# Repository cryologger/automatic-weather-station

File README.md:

# Cryologger - Automatic Weather Station (AWS)

### Note: This project is under active development.

## 1.0 Introduction
Polar environments are undergoing rapid environmental change, yet there is a lack of high spatial and temporal monitoring data available in these remote regions. Reliance on expensive and proprietary commercial data acquisition and telemetry systems can inhibit both researchers and citizen scientists and present a significant barrier to the establishment of widespread monitoring networks. The development of low-cost, open-source instrumentation can greatly reduce the cost of cryospheric research, improve the spatial density and coverage of collected data, and produce new ways to observe and monitor the cryosphere.

The Cryologger Automatic Weather Station (AWS), is an open-source datalogger and telemeter comprised of low-cost, off the shelf components that is capable of supporting the physical measurement needs of a variety of cryospheric scientific applications when configured as an automatic weather station (AWS).

## 2.0 Methods

### 2.1 Design
The Cryologger AWS is based on the open-source Arduino platform (www.arduino.cc) and built using low-cost, do-it-yourself electronics that can be easily modified to meet the needs of the end-user. Code was written using the Arduino Integrated Development Environment (IDE) and benefits from the availability of community-generated libraries.

Planned for extended deployments in harsh Arctic conditions, the Cryologger AWS provides long-term measurements of weather variables such as temperature, humidity, wind speed, wind direction, solar irradiance and snow depth, as well as system diagnostic variables including pitch, roll, battery voltage. Data are transmitted over the Iridium satellite network at specified intervals and can be remotely updated based on the desired sampling frequency. Collected data are made available in near-real time at https://cryologger.org.

#### 2.1.1. Bill of Materials (BOM)

For a complete bill of materials, including requirements for power and mounting of a complete deployable system, please see ASSEMBLY.md.

**Table 1.** Bill of materials and associated costs for the main components used in the Cryologger AWS v1.0. Prices are listed in USD and are current as of December 2023. Taxes and shipping not included. <sup>1</sup>Denotes optional component.
| Component             | Product                                                                                                                      | Quantity | Cost (USD) |
|-----------------------|------------------------------------------------------------------------------------------------------------------------------|:--------:|:----------:|
| PCB                   | [Custom Cryologger Printed Circuit Board](https://jlcpcb.com)                                                                |     1    |    $5.00   |
| Satellite transceiver | [Rock7 RockBLOCK 9603](http://www.rock7mobile.com/products-rockblock-9603)                                                   |     1    |   $267.50  |
| Satellite antenna     | [Maxtena M1621HCT-P-SMA](https://maxtena.com/products/f-passive/m1621hct-p-sma-iridium-passive-antenna/)                     |     1    |   $54.00   |
| Processor             | [Adafruit Feather M0 Adalogger](https://www.adafruit.com/product/2796)                                                       |     1    |   $19.95   |
| GNSS                  | [Adafruit Ultimate GPS FeatherWing](https://www.adafruit.com/product/3133)                                                   |     1    |   $24.95   |
| IMU                   | [Adafruit LSM303AGR Accelerometer Magnetometer](https://www.adafruit.com/product/4413)                                       |     1    |   $12.50   |
| Sensor                | [Adafruit BME280 Temperature Humidity Pressure Sensor ](https://www.adafruit.com/product/2652)                               |     1    |   $14.95   |
| Voltage regulator     | [Pololu D36V6F3 3.3V 600mA Step-Down Voltage Regulator](https://www.pololu.com/product/3791)                                 |     1    |   $16.95   |
| Voltage regulator     | [Pololu D36V6F5 5V 600mA Step-Down Voltage Regulator](https://www.pololu.com/product/3792)                                   |     1    |   $16.95   |
| Voltage regulator     | [Pololu U3V40F12 12V Step-Up Voltage Regulator ](https://www.pololu.com/product/4016)                                        |     1    |    $9.95   |
| Resistor              | [10 M 1% 0.6 W resistor](https://www.mouser.ca/ProductDetail/594-MBB02070C1005FCT)                                           |     1    |    $0.44   |
| Resistor              | [1 M 1% 0.6 W resistor](https://www.mouser.ca/ProductDetail/594-B0207C1M000F5T)                                              |     1    |    $0.40   |
| Capacitor             | [0.1 uF Capacitor](https://www.mouser.ca/ProductDetail/Vishay-BC-Components/K104K15X7RF53L2?qs=mWFvmKOfYW8KbAXlf9eSQA%3D%3D) |     1    |    $0.29   |
| Power connector       |                                                                                                                              |     1    |            |
| Power connector       |                                                                                                                              |     1    |            |
| Connector             |                                                                                                                              |     1    |            |

**Table 2.** Environmental sensors used in Cryologger AWS v1.0. Prices are listed in USD and are current as of December 2023. Taxes and shipping not included.
| Environment Variable          | Sensor                                                                                                                       | Cost (USD) |
|-------------------------------|------------------------------------------------------------------------------------------------------------------------------|:----------:|
| Wind Speed & Direction        | [RM Young Wind Monitor 5103L Anemometer](https://www.youngusa.com/product/wind-monitor/)                                     | $1432      |
| Temperature/Relative Humidity | [Vaisala HMP60 Humidity and Temperature Probe](https://store.vaisala.com/en/products/HMP60)                                  | $330       |
| Solar Irradiance              | [SP-212-SS: Amplified 0-2.5 Volt Pyranometer](https://www.apogeeinstruments.com/sp-212-ss-amplified-0-2-5-volt-pyranometer/) | $325       |
| Snow Depth                    | [Maxboxtix MB7374 HRXL-MaxSonar-WRST7](https://maxbotix.com/products/mb7374)                                                 | $290       |

### 2.2 Operation
When initially powered on, the Cryologger AWS will attempt to establish a GNSS fix and sychronize the real-time clock (RTC) for up to 5 minutes. Once the RTC is synchronized, the system will set an alarm to wake at the user-specified time and then enter a low-power deep sleep. Nominally, the system will wake every 5 minutes, obtain measurements from all sensors, and log data to a microSD card. Measurements are averaged each hour and transmitted  

While the system is in deep sleep, a Watchdog Timer (WDT) will wake the system to check the program has not frozen every 8 seconds and perform a reset, if necessary. This helps to ensure the long-term reliability of the system.

#### 2.2.1 Measurements

**Table 2.** List of Cryologger AWS v1.0 data variables that can be transmitted and/or logged with variable sizes.

| Type     | Variable          | Description                        | Size (bytes) |
|----------|-------------------|------------------------------------|:------------:|
| uint32_t | unixtime          | UNIX Epoch time                    |       4      |
| int16_t  | temperatureInt    | Internal temperature (°C)          |       2      |
| uint16_t | humidityInt       | Internal humidity (%)              |       2      |
| uint16_t | pressureInt       | Internal pressure (hPa)            |       2      |
| int16_t  | temperatureExt    | External temperature (°C)          |       2      |
| uint16_t | humidityExt       | External humidity (%)              |       2      |
| int16_t  | pitch             | Pitch (°)                          |       2      |
| int16_t  | roll              | Roll (°)                           |       2      |
| uint16_t | solar             | Solar irradiance (W m-2)           |       2      |
| uint16_t | windSpeed         | Mean wind speed (m/s)              |       2      |
| uint16_t | windDirection     | Mean wind direction (°)            |       2      |
| uint16_t | windGustSpeed     | Wind gust speed (m/s)              |       2      |
| uint16_t | windGustDirection | Wind gust direction (°)            |       2      |
| int32_t  | latitude          | Latitude (DD)                      |       4      |
| int32_t  | longitude         | Longitude (DD)                     |       4      |
| uint8_t  | satellites        | Number of satellites               |       1      |
| uint16_t | hdop              | HDOP                               |       2      |
| uint16_t | voltage           | Battery voltage (V)                |       2      |
| uint16_t | transmitDuration  | Previous transmission duration (s) |       2      |
| uint8_t  | transmitStatus    | Iridium return code                |       1      |
| uint16_t | iterationCounter  | Message counter                    |       2      |

#### 2.2.2 Data Transmission and Processing

Sensor measurements and GNSS position are recorded hourly and stored in memory until the desired transmission interval is reached. Data are compressed into a binary message (340 bytes maximum) to minimize the cost and total number of transmissions required. Data are transmitted via the Iridium Short Burst Data (SBD) satellite network at user-specified intervals, which can be remotely updated based on the desired sampling frequency. SBD data messages are received by an Iridium ground station and sent to Ground Control's server. The data is then forwarded to an Amazon Web Services (AWS) SQS queue, decoded using an AWS Lambda Python function and stored in a database using the Amazon Relational Database Service (RDS). Data can be viewed in near-real time at https://cryologger.org.

## 3.0 Deployments

<p align="center"><b>Figure 3.</b> Map of Cryologger AWS deployments made between 2019 and 2023.</p>

## 4.0 Results

## 5.0 Conclusion

## Repository Contents

* **/Documentation** - Assembly, deployment and troubleshoting guides, as well as information of components used and associated costs.

* **/Hardware** - KiCad PCB schematic and design files.

* **/Software** - Arduino code and Python data analysis scripts.

## License Information
Cryologger code, firmware, and software is licensed under the GNU General Public License v3.0 (https://www.gnu.org/licenses/gpl-3.0.en.html). 

<p xmlns:cc="http://creativecommons.org/ns#" >Cryologger hardware is licensed under <a href="https://creativecommons.org/licenses/by-nc-sa/4.0/?ref=chooser-v1" target="_blank" rel="license noopener noreferrer" style="display:inline-block;">CC BY-NC-SA 4.0 </a></p>

Cheers,

**Adam**

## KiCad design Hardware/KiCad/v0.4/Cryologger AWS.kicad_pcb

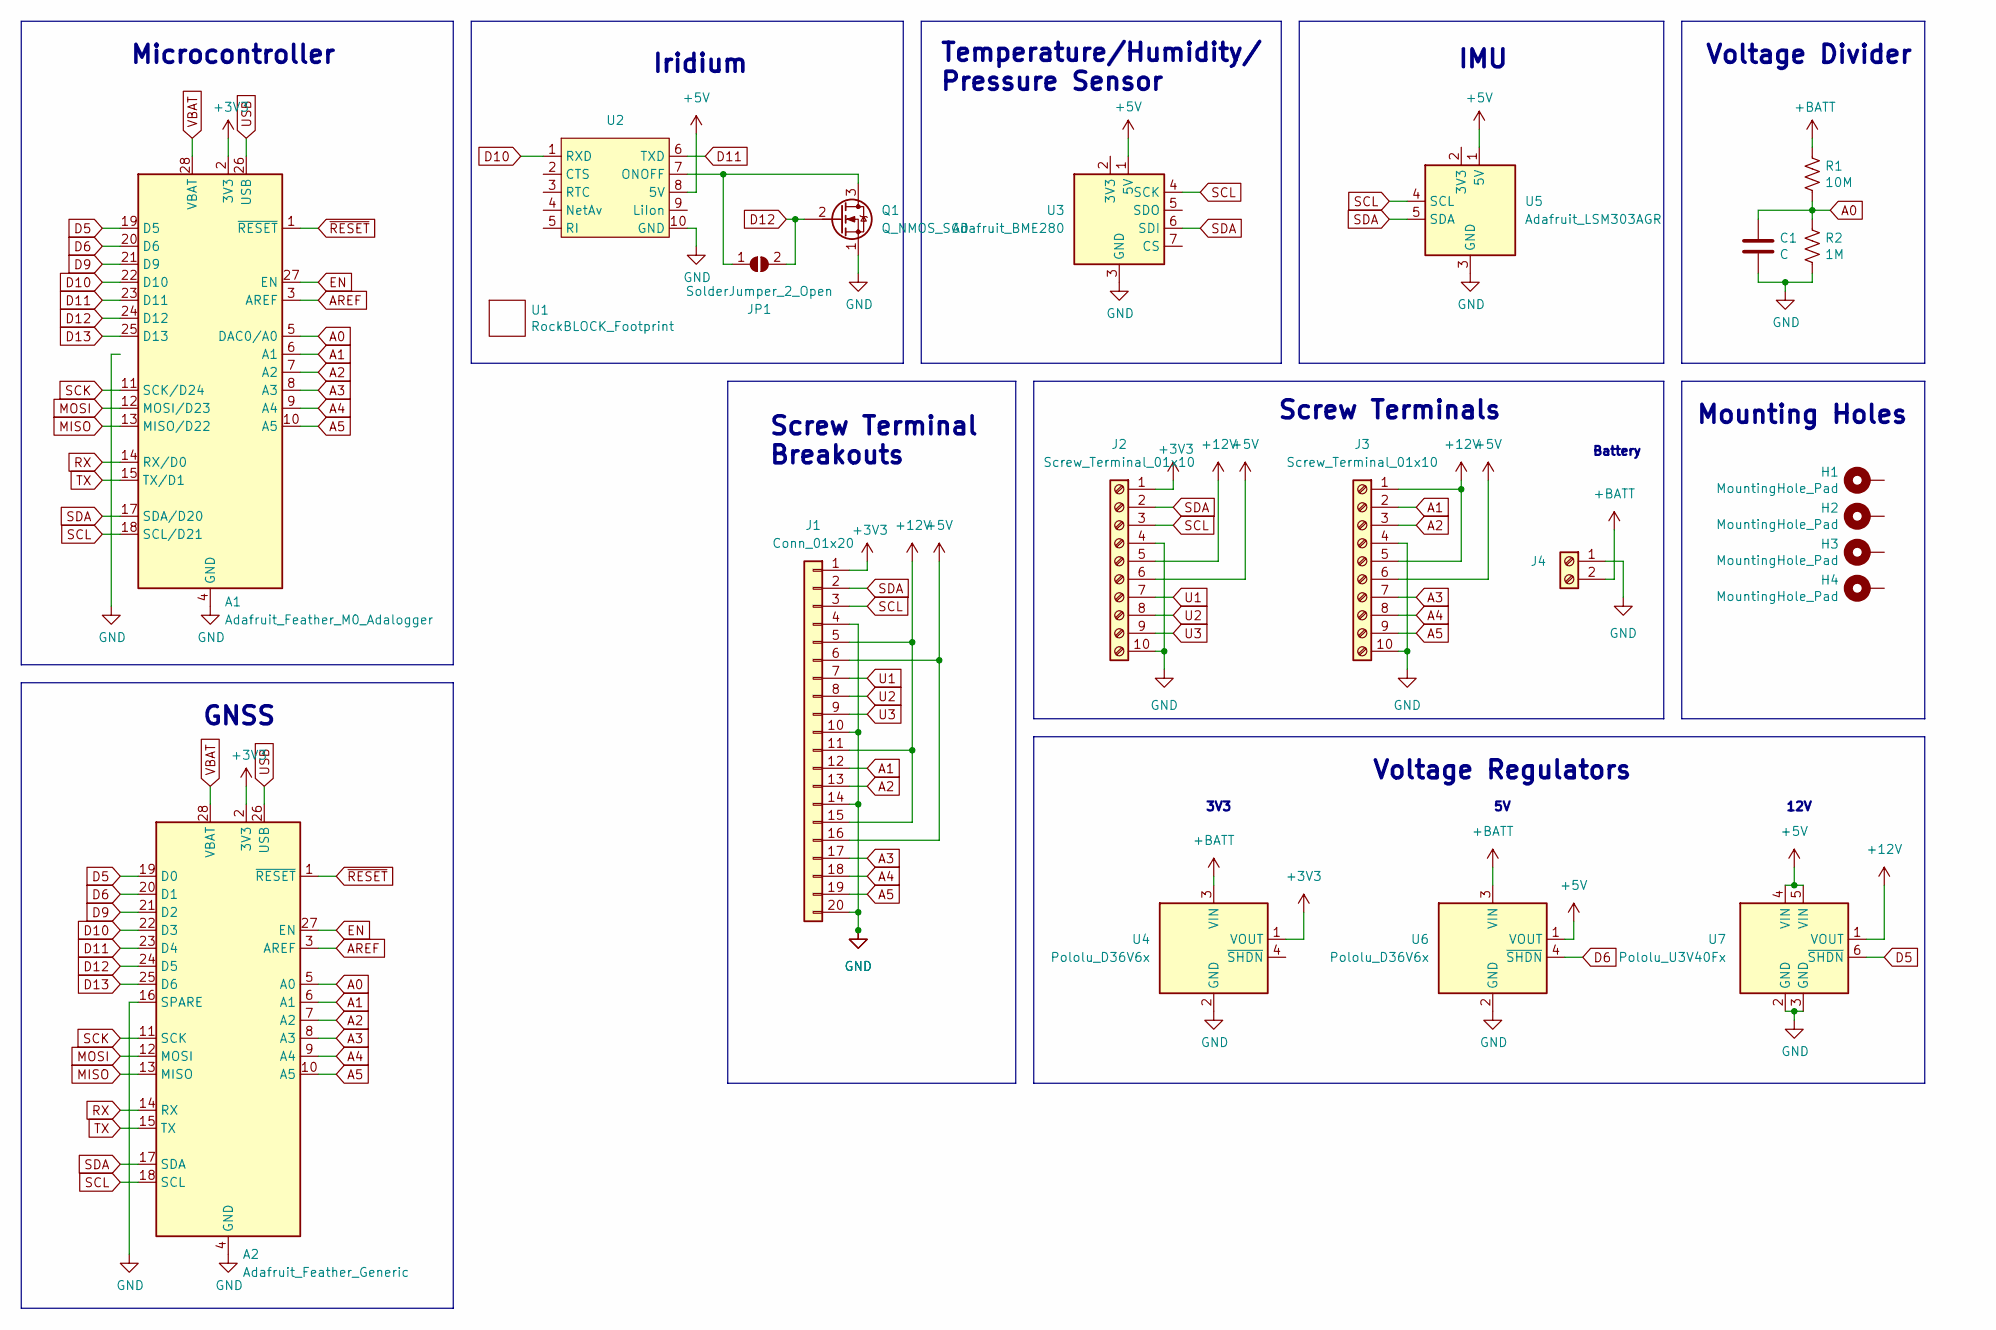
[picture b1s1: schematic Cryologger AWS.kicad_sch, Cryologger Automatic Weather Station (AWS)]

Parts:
A1: Adafruit_Feather_M0_Adalogger; Adafruit_Feather_Header_Double
A2: Adafruit_Feather_Generic; Adafruit_Feather_Header_Double
C1: C; C_Disc_D3.8mm_W2.6mm_P2.50mm
H1, H2, H3, H4: MountingHole_Pad; MountingHole_3mm_Pad
J1: Conn_01x20; Pin_1.0mm_10.0mm_1x20
J2, J3: Screw_Terminal_01x10; TerminalBlock_Phoenix_MKDS-1,5-10-5.08_1x10_P5.08mm_Horizon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
J4: Screw_Terminal_01x02; PhoenixContact_MSTBA_2,5_2-G-5,08_1x02_P5.08mm_Horizontal
JP1: SolderJumper_2_Open; SolderJumper-2_P1.3mm_Open_RoundedPad1.0x1.5mm
Q1: Q_NMOS_SGD; TO-92
R1: 10M; R_Axial_DIN0207_L6.3mm_D2.5mm_P10.16mm_Horizontal
R2: 1M; R_Axial_DIN0207_L6.3mm_D2.5mm_P10.16mm_Horizontal
U1: RockBLOCK_Footprint; RockBLOCK_9603
U2: Molex_PicoBlade_53047-1010_1x10_P1.25mm_Vertical
U3: Adafruit_BME280
U4, U6: Pololu_D36V6x
U5: Adafruit_LSM303AGR
U7: Pololu_U3V40Fx

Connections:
+3V3: A1.2 (3V3), A2.2 (3V3), J1.1, J2.1, U4.1 (VOUT)
+5V: J1.6, J1.16, J2.6, J3.6, U2.8 (5V), U3.1 (5V), U5.1 (5V), U6.1 (VOUT), U7.4 (VIN), U7.5 (VIN)
+12V: J1.5, J1.11, J1.15, J2.5, J3.1, J3.5, U7.1 (VOUT)
+BATT: J4.2, R1.1, U4.3 (VIN), U6.3 (VIN)
A0: A1.5 (DAC0/A0), A2.5 (A0), C1.1, R1.2, R2.1
A1: A1.6 (A1), A2.6 (A1), J1.12, J3.2
A2: A1.7 (A2), A2.7 (A2), J1.13, J3.3
A3: A1.8 (A3), A2.8 (A3), J1.17, J3.7
A4: A1.9 (A4), A2.9 (A4), J1.18, J3.8
A5: A1.10 (A5), A2.10 (A5), J1.19, J3.9
AREF: A1.3 (AREF), A2.3 (AREF)
D5: A1.19 (D5), A2.19 (D0), U7.6 (~SHDN)
D6: A1.20 (D6), A2.20 (D1), U6.4 (~SHDN)
D9: A1.21 (D9), A2.21 (D2)
D10: A1.22 (D10), A2.22 (D3), U2.1 (RXD)
D11: A1.23 (D11), A2.23 (D4), U2.6 (TXD)
D12: A1.24 (D12), A2.24 (D5), JP1.2 (B), Q1.2 (G)
D13: A1.25 (D13), A2.25 (D6)
EN: A1.27 (EN), A2.27 (EN)
GND: A1.4 (GND), A1.16 (GND), A2.4 (GND), A2.16 (SPARE), C1.2, J1.4, J1.10, J1.14, J1.20, J2.4, J2.10, J3.4, J3.10, J4.1, Q1.1 (S), R2.2, U2.10 (GND), U3.3 (GND), U4.2 (GND), U5.3 (GND), U6.2 (GND), U7.2 (GND), U7.3 (GND)
MISO: A1.13 (MISO/D22), A2.13 (MISO)
MOSI: A1.12 (MOSI/D23), A2.12 (MOSI)
unnamed: JP1.1 (A), Q1.3 (D), U2.7 (ONOFF)
RX: A1.14 (RX/D0), A2.14 (RX)
SCK: A1.11 (SCK/D24), A2.11 (SCK)
SCL: A1.18 (SCL/D21), A2.18 (SCL), J1.3, J2.3, U3.4 (SCK), U5.4 (SCL)
SDA: A1.17 (SDA/D20), A2.17 (SDA), J1.2, J2.2, U3.6 (SDI), U5.5 (SDA)
TX: A1.15 (TX/D1), A2.15 (TX)
U1: J1.7, J2.7
U2: J1.8, J2.8
U3: J1.9, J2.9
USB: A1.26 (USB), A2.26 (USB)
VBAT: A1.28 (VBAT), A2.28 (VBAT)
~RESET: A1.1 (~RESET), A2.1 (~RESET)

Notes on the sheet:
Screw Terminals
Iridium
Voltage Regulators
Voltage Divider
GNSS
IMU
Microcontroller
Screw Terminal Breakouts
3V3
Battery
Temperature/Humidity/ Pressure Sensor
12V
Mounting Holes

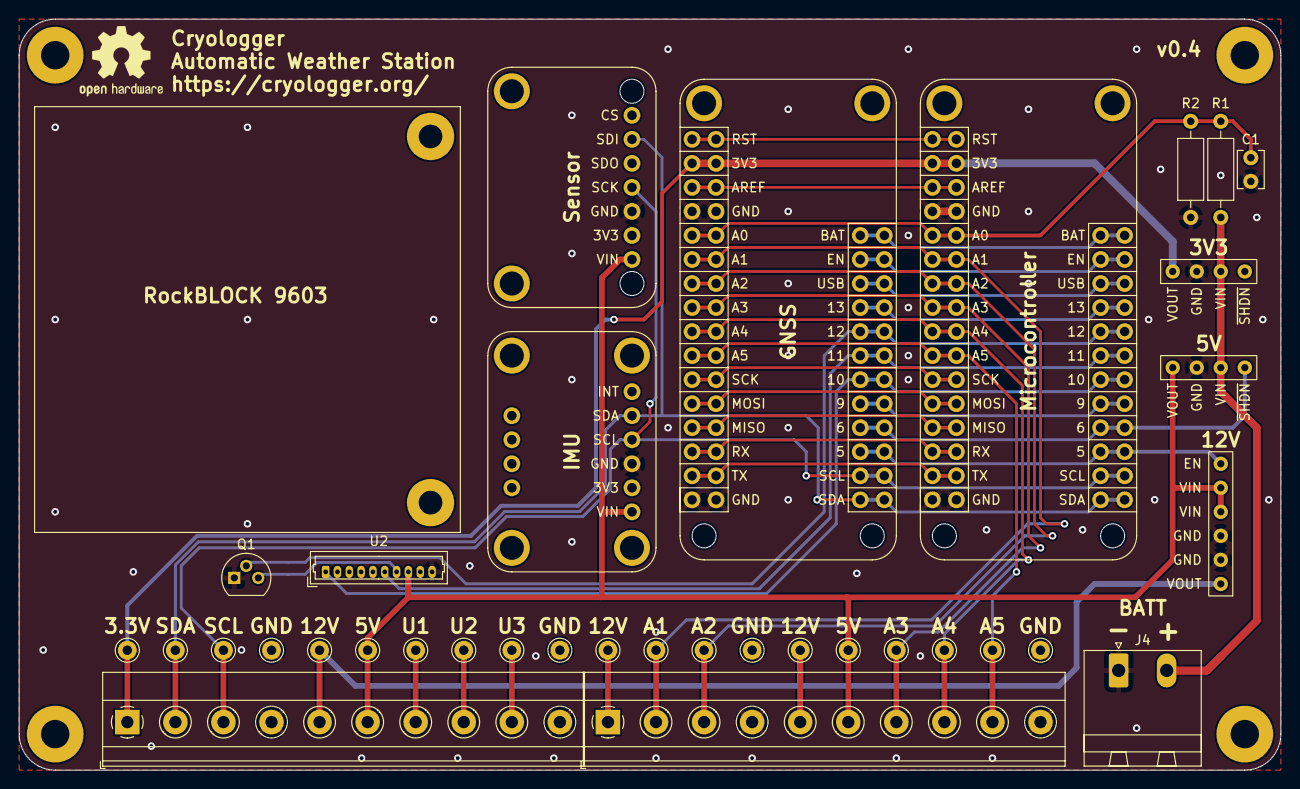
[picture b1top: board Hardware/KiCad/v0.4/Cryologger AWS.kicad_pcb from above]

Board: 2 copper layers, 133.3 x 79.4 mm, 22 parts (1 on the bottom side), 34 nets.

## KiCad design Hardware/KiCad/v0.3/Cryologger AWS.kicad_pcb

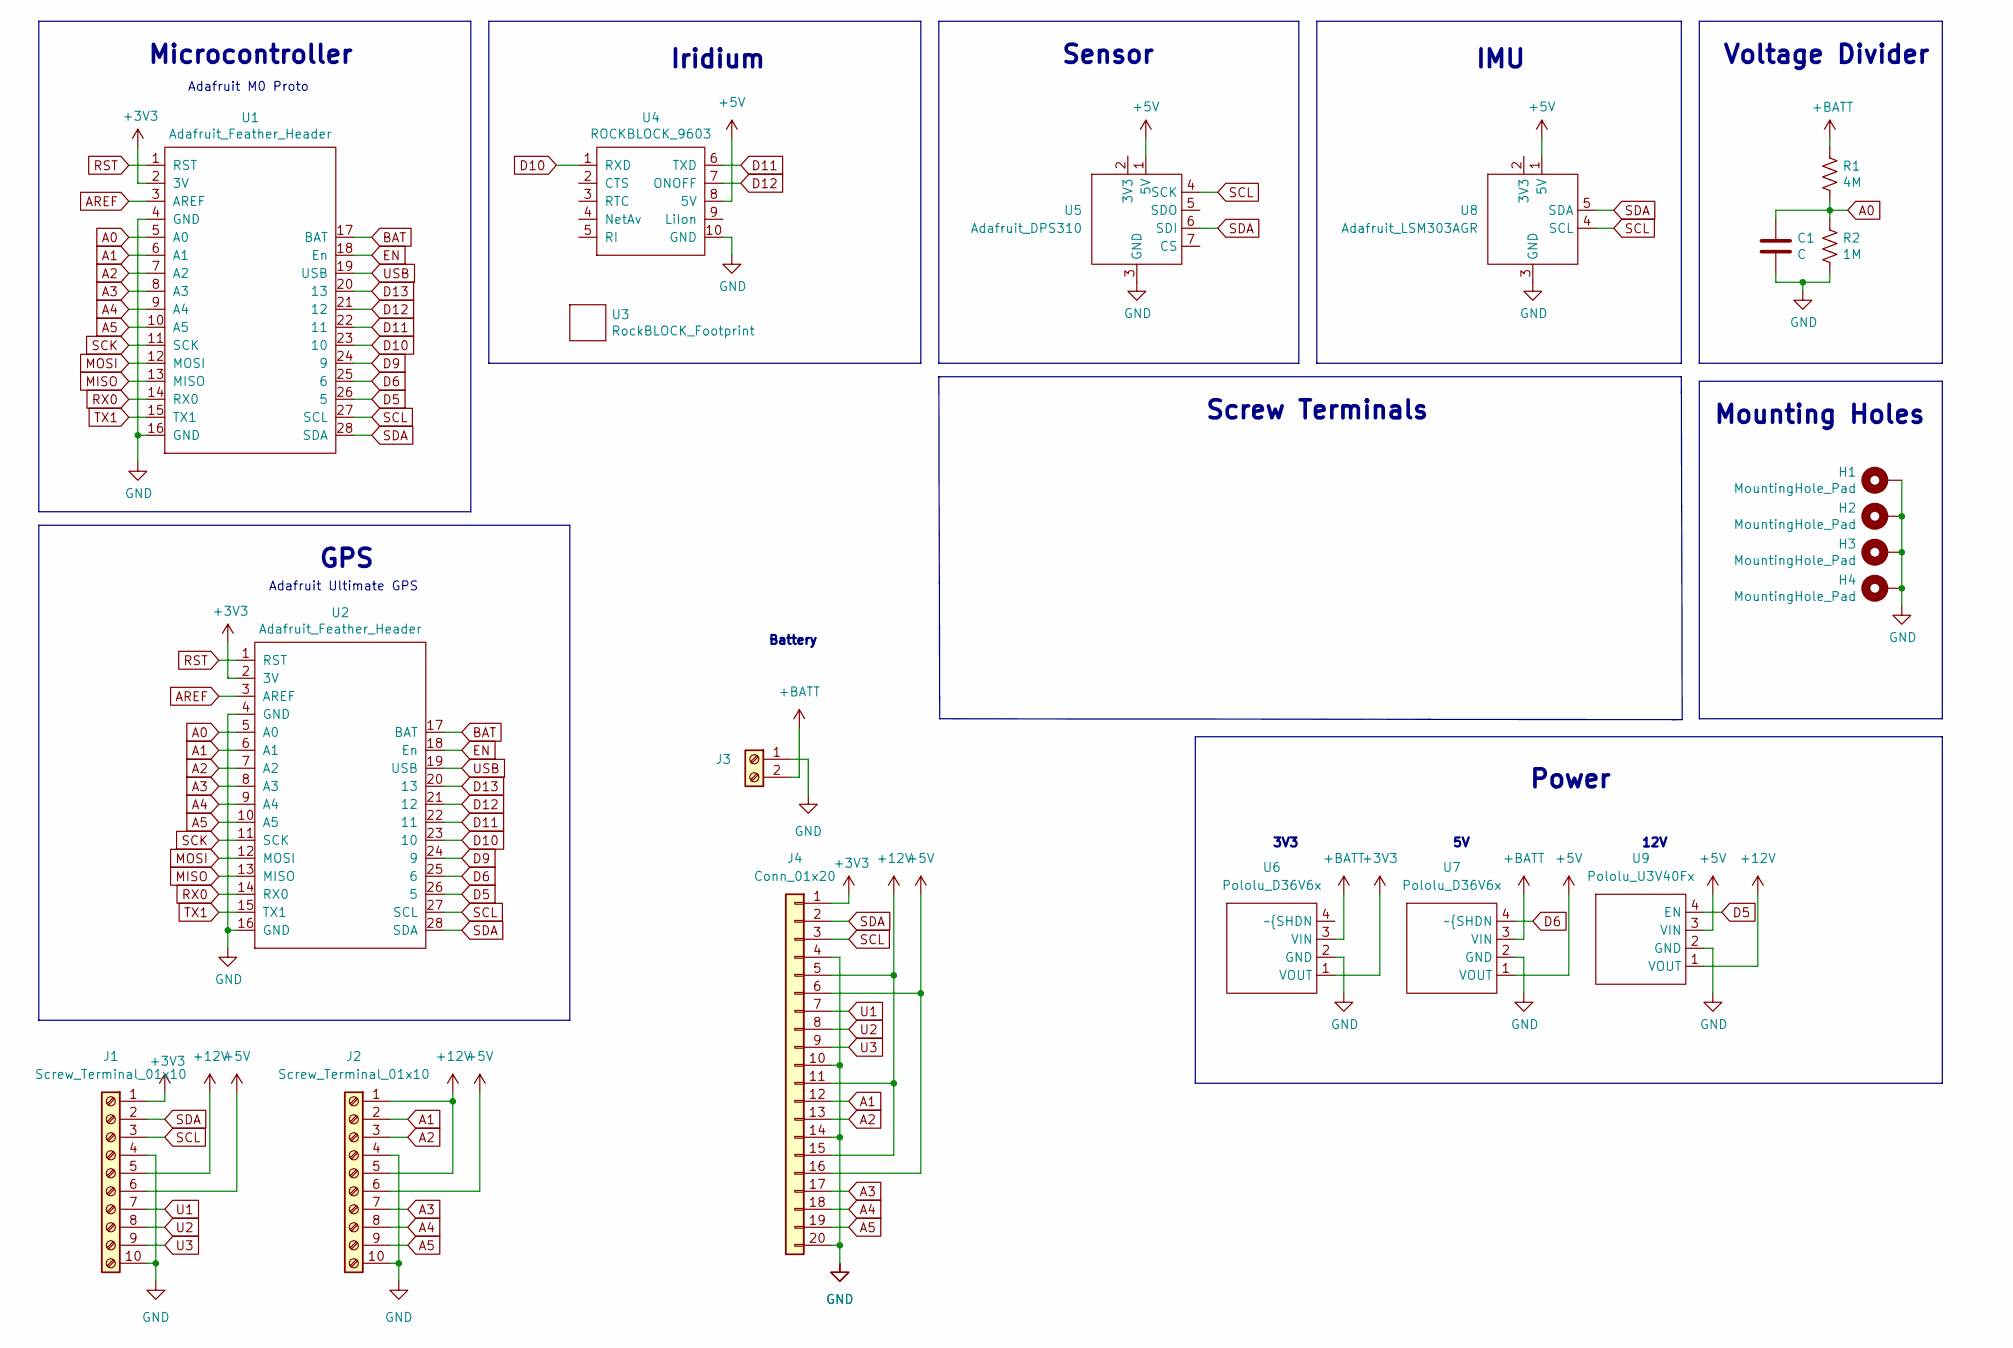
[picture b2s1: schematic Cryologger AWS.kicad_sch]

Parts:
C1: C; C_Disc_D3.8mm_W2.6mm_P2.50mm
H1, H2, H3, H4: MountingHole_Pad; MountingHole_3mm_Pad
J1, J2: Screw_Terminal_01x10; TerminalBlock_Phoenix_MKDS-1,5-10-5.08_1x10_P5.08mm_Horizon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
J3: Screw_Terminal_01x02; PhoenixContact_MSTBA_2,5_2-G-5,08_1x02_P5.08mm_Horizontal
J4: Conn_01x20; Pin_1.0mm_10.0mm_1x20
R1: 4M; R_Axial_DIN0207_L6.3mm_D2.5mm_P10.16mm_Horizontal
R2: 1M; R_Axial_DIN0207_L6.3mm_D2.5mm_P10.16mm_Horizontal
U1, U2: Adafruit_Feather_Header; Adafruit_Feather_Header_Double
U3: RockBLOCK_Footprint; RockBLOCK_9603
U4: ROCKBLOCK_9603; Molex_PicoBlade_53047-1010_1x10_P1.25mm_Vertical
U5: Adafruit_DPS310
U6, U7: Pololu_D36V6x
U8: Adafruit_LSM303AGR
U9: Pololu_U3V40Fx

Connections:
+3V3: J1.1, J4.1, U1.2 (3V), U2.2 (3V), U6.1 (VOUT)
+5V: J1.6, J2.6, J4.6, J4.16, U4.8 (5V), U5.1 (5V), U7.1 (VOUT), U8.1 (5V), U9.3 (VIN)
+12V: J1.5, J2.1, J2.5, J4.5, J4.11, J4.15, U9.1 (VOUT)
+BATT: J3.2, R1.1, U6.3 (VIN), U7.3 (VIN)
A0: C1.1, R1.2, R2.1, U1.5 (A0), U2.5 (A0)
A1: J2.2, J4.12, U1.6 (A1), U2.6 (A1)
A2: J2.3, J4.13, U1.7 (A2), U2.7 (A2)
A3: J2.7, J4.17, U1.8 (A3), U2.8 (A3)
A4: J2.8, J4.18, U1.9 (A4), U2.9 (A4)
A5: J2.9, J4.19, U1.10 (A5), U2.10 (A5)
AREF: U1.3 (AREF), U2.3 (AREF)
BAT: U1.17 (BAT), U2.17 (BAT)
D5: U1.26 (5), U2.26 (5), U9.4 (EN)
D6: U1.25 (6), U2.25 (6), U7.4 (~{SHDN)
D9: U1.24 (9), U2.24 (9)
D10: U1.23 (10), U2.23 (10), U4.1 (RXD)
D11: U1.22 (11), U2.22 (11), U4.6 (TXD)
D12: U1.21 (12), U2.21 (12), U4.7 (ONOFF)
D13: U1.20 (13), U2.20 (13)
EN: U1.18 (En), U2.18 (En)
GND: C1.2, H1.1, H2.1, H3.1, H4.1, J1.4, J1.10, J2.4, J2.10, J3.1, J4.4, J4.10, J4.14, J4.20, R2.2, U1.4 (GND), U1.16 (GND), U2.4 (GND), U2.16 (GND), U4.10 (GND), U5.3 (GND), U6.2 (GND), U7.2 (GND), U8.3 (GND), U9.2 (GND)
MISO: U1.13 (MISO), U2.13 (MISO)
MOSI: U1.12 (MOSI), U2.12 (MOSI)
RST: U1.1 (RST), U2.1 (RST)
RX0: U1.14 (RX0), U2.14 (RX0)
SCK: U1.11 (SCK), U2.11 (SCK)
SCL: J1.3, J4.3, U1.27 (SCL), U2.27 (SCL), U5.4 (SCK), U8.4 (SCL)
SDA: J1.2, J4.2, U1.28 (SDA), U2.28 (SDA), U5.6 (SDI), U8.5 (SDA)
TX1: U1.15 (TX1), U2.15 (TX1)
U1: J1.7, J4.7
U2: J1.8, J4.8
U3: J1.9, J4.9
USB: U1.19 (USB), U2.19 (USB)

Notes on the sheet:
Screw Terminals
Iridium
Power
Voltage Divider
IMU
Microcontroller
Adafruit Ultimate GPS
3V3
Adafruit M0 Proto
Battery
Sensor
GPS
12V
Mounting Holes

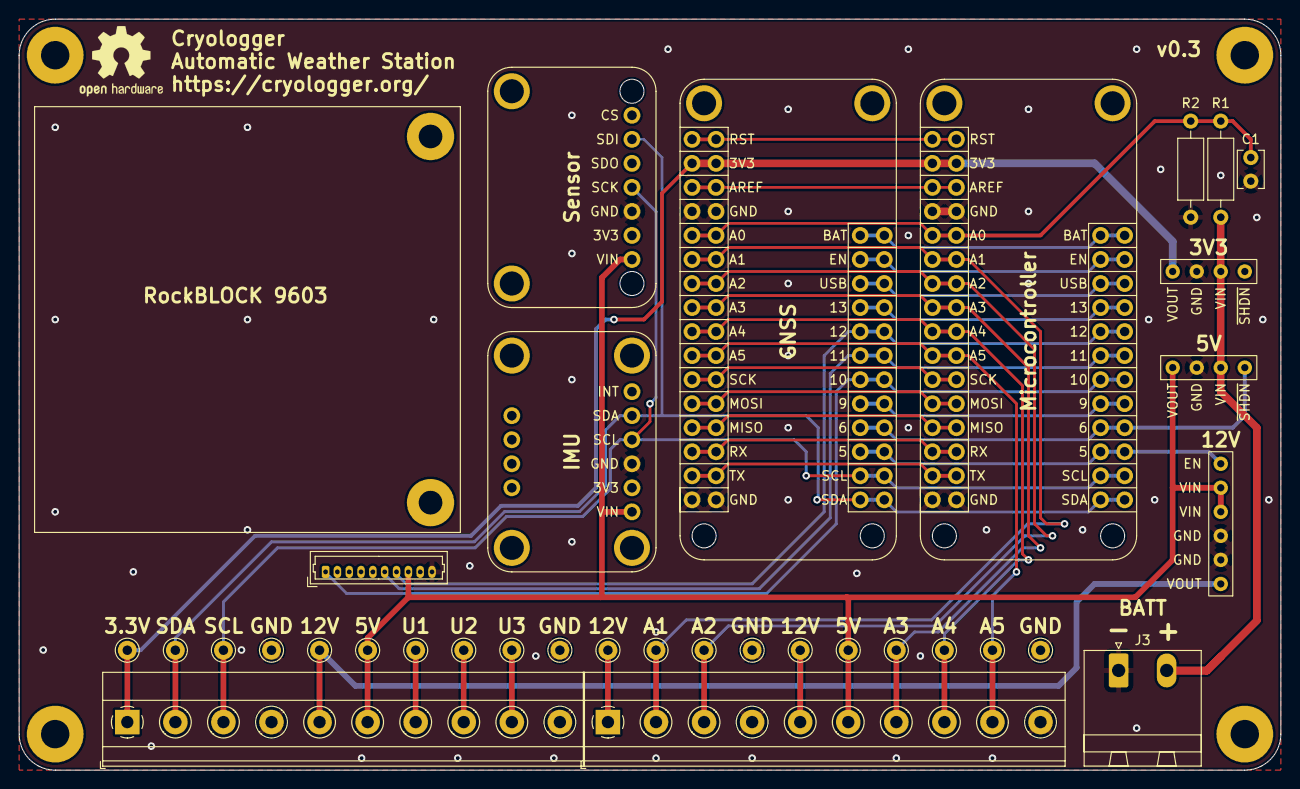
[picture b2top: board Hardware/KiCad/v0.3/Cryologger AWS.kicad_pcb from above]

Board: 2 copper layers, 133.3 x 79.4 mm, 20 parts (0 on the bottom side), 33 nets.

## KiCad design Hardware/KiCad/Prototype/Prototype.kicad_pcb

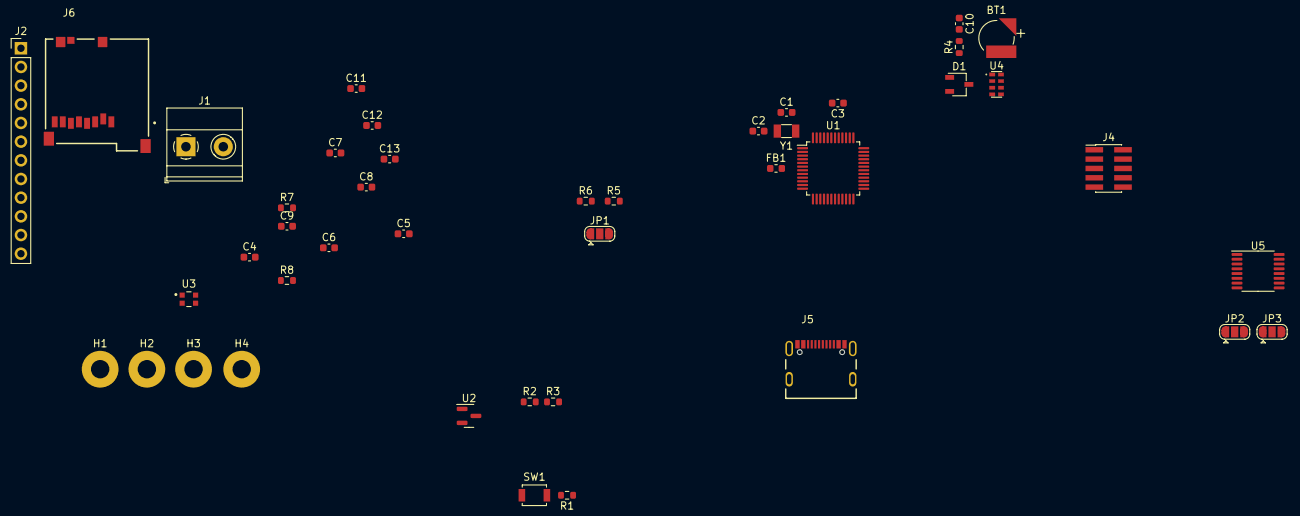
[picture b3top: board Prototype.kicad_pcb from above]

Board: 2 copper layers, 43 parts (0 on the bottom side), 28 nets, no tracks yet.

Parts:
BT1: ML414H; SEIKO_ML414H_IV01E
C1, C2: 22nF; C_0603_1608Metric
C3, C4, C5, C6, C9, C10, C11, C12, C13: 0.1uF; C_0603_1608Metric
C7, C8: 1uF; C_0603_1608Metric
D1: BAS70-05; TSOT-23
FB1: FerriteBead; L_0603_1608Metric
H1, H2, H3, H4: MountingHole; MountingHole_2.5mm_Pad
J1: Screw_Terminal_01x02; TerminalBlock_Phoenix_MKDS-1,5-2-5.08_1x02_P5.08mm_Horizont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
J2: Conn_01x12; PinHeader_1x12_P2.54mm_Vertical
J4: Conn_ARM_JTAG_SWD_10; PinHeader_2x05_P1.27mm_Vertical_SMD
J5: USB_C_Receptacle_USB2.0; GCT_USB4105-GF-A
J6: Micro_SD_Card; GCT_MEM2051-00-195-00-A_REVD1
JP1: SolderJumper_3_Bridged123; SolderJumper-3_P1.3mm_Open_RoundedPad1.0x1.5mm
JP2, JP3: SolderJumper_3_Bridged12; SolderJumper-3_P1.3mm_Open_RoundedPad1.0x1.5mm
R1: 10k; R_0603_1608Metric
R2: 4M; R_0603_1608Metric
R3: 1M; R_0603_1608Metric
R4: 3.3k; R_0603_1608Metric
R5, R6: 2.2k; R_0603_1608Metric
R7, R8: 5.1k; R_0603_1608Metric
SW1: SW_SPST; SW_SPST_B3U-1000P
U1: ATSAMD21G18A-A; TQFP-48_7x7mm_P0.5mm
U2: MCP1703A-3302_SOT23; SOT-23
U3: WS2812_2020; LED_WS2812-2020
U4: RV-8803-C7; MICROCRYSTAL_RV-8803-C7-TA-QC
U5: ADS122C04IPW; TSSOP-16_4.4x5mm_P0.65mm
Y1: 32.768kHz; Crystal_SMD_3215-2Pin_3.2x1.5mm

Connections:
+3V3: C4.2, C5.1, C8.2, C11.2, C13.2, D1.1 (K), D1.2 (K), FB1.1, JP1.2 (C), JP2.3 (B), JP3.3 (B), R1.2, U1.17 (VDDIO), U1.36 (VDDIO), U1.44 (VDDIN), U2.2 (VO), U3.4 (VDD), U5.13 (DVDD)
+5V: C12.2, U5.12 (AVDD)
+BATT: C7.2, J1.1, R2.2, U2.3 (VI)
ADDR_A0: JP2.2 (C), U5.1 (A0)
ADDR_A1: JP3.2 (C), U5.2 (A1)
D5: U1.24 (PA15), U4.6 (~{INT)
D9/A7: C9.2, R2.1, R3.2, U1.12 (PA07)
D10: U1.27 (PA18), U3.3 (DI)
GND: BT1.2 (-), C1.1, C2.1, C3.1, C4.1, C5.2, C6.2, C7.1, C8.1, C9.1, C10.1, C11.1, C12.1, C13.1, J1.2, J5.S1 (SHIELD), J6.6 (VSS), JP2.1 (A), JP3.1 (A), R3.1, R7.2, R8.2, SW1.1 (A), U1.5 (GNDANA), U1.18 (GND), U1.35 (GND), U1.42 (GND), U2.1 (GND), U3.2 (GND), U4.2 (CLKOUT), U4.4 (CLKOE), U4.5 (VSS), U4.7 (EVI), U5.4 (DGND), U5.5 (AVSS)
unnamed: BT1.1 (+), R4.1
unnamed: C1.2, U1.1 (PA00), Y1.2
unnamed: C2.2, U1.2 (PA01), Y1.1
unnamed: C3.2, U1.43 (VDDCORE)
unnamed: C6.1, FB1.2, U1.6 (VDDANA)
unnamed: C10.2, D1.3 (A), R4.2, U4.3 (VDD)
unnamed: J4.3 (GND), J4.5 (GND)
unnamed: J5.A5 (CC1), R7.1
unnamed: J5.B5 (CC2), R8.1
unnamed: JP1.1 (A), R6.2
unnamed: JP1.3 (B), R5.2
unnamed: R1.1, SW1.2 (B), U1.40 (~RESET)
SCL: R5.1, U1.32 (PA23), U4.8 (SCL), U5.16 (SCL)
SDA: R6.1, U1.31 (PA22), U4.1 (SDA), U5.15 (SDA)
SPI_CIPO: J6.7 (DAT0), U1.21 (PA12)
SPI_COPI: J6.3 (CMD), U1.19 (PB10)
SPI_SCK: J6.5 (CLK), U1.20 (PB11)
USB_D+: J5.A6 (D+), J5.B6 (D+), U1.34 (PA25)
USB_D-: J5.A7 (D-), J5.B7 (D-), U1.33 (PA24)

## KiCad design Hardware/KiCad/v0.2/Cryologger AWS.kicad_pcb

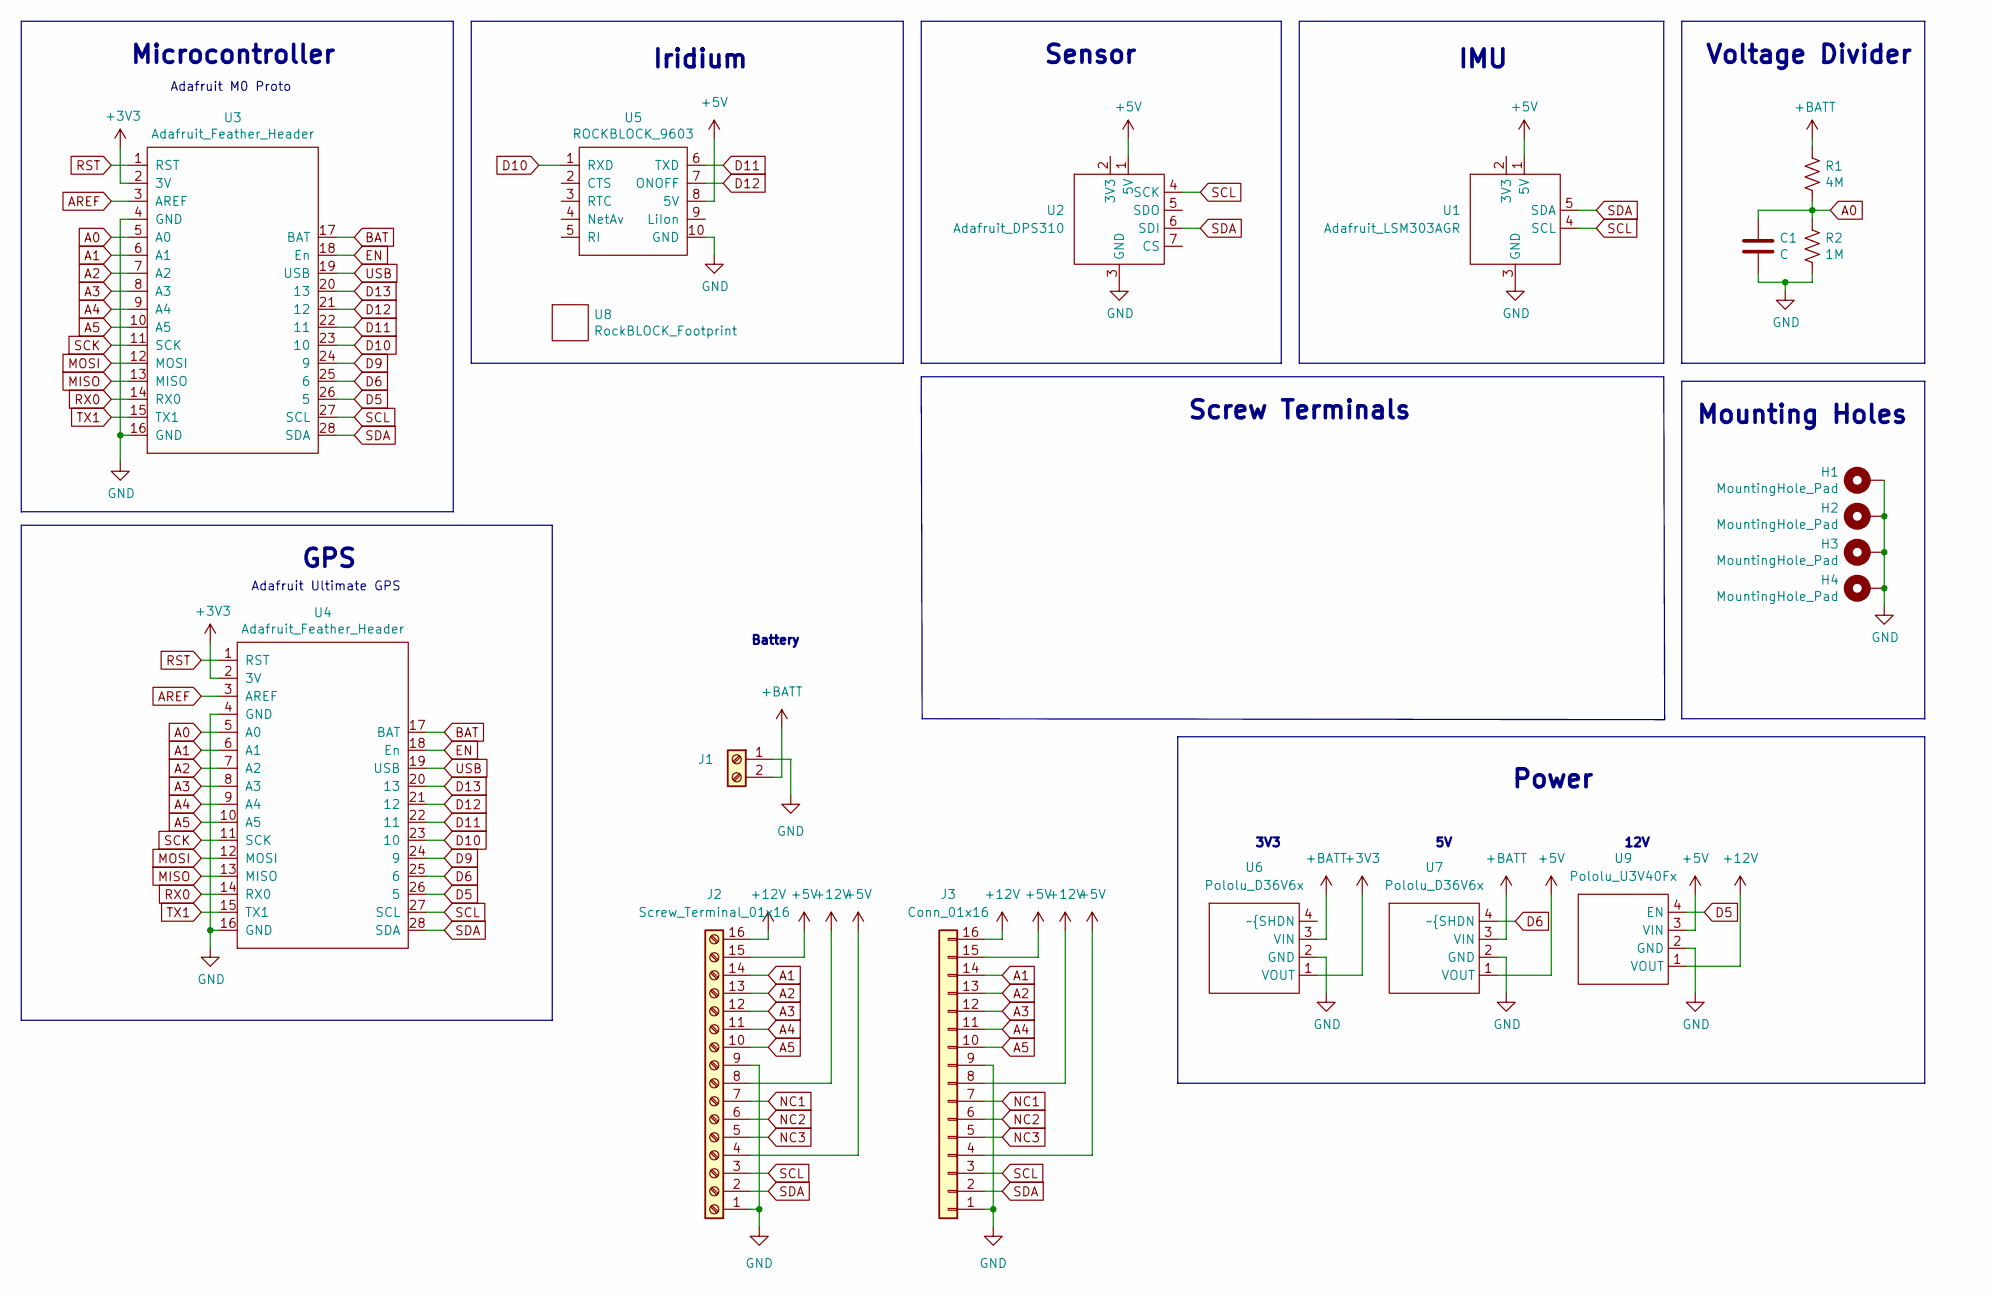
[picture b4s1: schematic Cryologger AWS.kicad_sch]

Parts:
C1: C; C_Disc_D3.8mm_W2.6mm_P2.50mm
H1, H2, H3, H4: MountingHole_Pad; MountingHole_3mm_Pad
J1: Screw_Terminal_01x02; PhoenixContact_MSTBA_2,5_2-G-5,08_1x02_P5.08mm_Horizontal
J2: Screw_Terminal_01x16; TerminalBlock_Phoenix_MKDS-1,5-16-5.08_1x16_P5.08mm_Horizon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
J3: Conn_01x16; Pin_1.0mm_10.0mm_1x16
R1: 4M; R_Axial_DIN0207_L6.3mm_D2.5mm_P10.16mm_Horizontal
R2: 1M; R_Axial_DIN0207_L6.3mm_D2.5mm_P10.16mm_Horizontal
U1: Adafruit_LSM303AGR
U2: Adafruit_DPS310
U3, U4: Adafruit_Feather_Header; Adafruit_Feather_Header_Double
U5: ROCKBLOCK_9603; Molex_PicoBlade_53047-1010_1x10_P1.25mm_Vertical
U6, U7: Pololu_D36V6x
U8: RockBLOCK_Footprint; RockBLOCK_9603
U9: Pololu_U3V40Fx

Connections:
+3V3: U3.2 (3V), U4.2 (3V), U6.1 (VOUT)
+5V: J2.4, J2.15, J3.4, J3.15, U1.1 (5V), U2.1 (5V), U5.8 (5V), U7.1 (VOUT), U9.3 (VIN)
+12V: J2.8, J2.16, J3.8, J3.16, U9.1 (VOUT)
+BATT: J1.2, R1.1, U6.3 (VIN), U7.3 (VIN)
A0: C1.1, R1.2, R2.1, U3.5 (A0), U4.5 (A0)
A1: J2.14, J3.14, U3.6 (A1), U4.6 (A1)
A2: J2.13, J3.13, U3.7 (A2), U4.7 (A2)
A3: J2.12, J3.12, U3.8 (A3), U4.8 (A3)
A4: J2.11, J3.11, U3.9 (A4), U4.9 (A4)
A5: J2.10, J3.10, U3.10 (A5), U4.10 (A5)
AREF: U3.3 (AREF), U4.3 (AREF)
BAT: U3.17 (BAT), U4.17 (BAT)
D5: U3.26 (5), U4.26 (5), U9.4 (EN)
D6: U3.25 (6), U4.25 (6), U7.4 (~{SHDN)
D9: U3.24 (9), U4.24 (9)
D10: U3.23 (10), U4.23 (10), U5.1 (RXD)
D11: U3.22 (11), U4.22 (11), U5.6 (TXD)
D12: U3.21 (12), U4.21 (12), U5.7 (ONOFF)
D13: U3.20 (13), U4.20 (13)
EN: U3.18 (En), U4.18 (En)
GND: C1.2, H1.1, H2.1, H3.1, H4.1, J1.1, J2.1, J2.9, J3.1, J3.9, R2.2, U1.3 (GND), U2.3 (GND), U3.4 (GND), U3.16 (GND), U4.4 (GND), U4.16 (GND), U5.10 (GND), U6.2 (GND), U7.2 (GND), U9.2 (GND)
MISO: U3.13 (MISO), U4.13 (MISO)
MOSI: U3.12 (MOSI), U4.12 (MOSI)
NC1: J2.7, J3.7
NC2: J2.6, J3.6
NC3: J2.5, J3.5
RST: U3.1 (RST), U4.1 (RST)
RX0: U3.14 (RX0), U4.14 (RX0)
SCK: U3.11 (SCK), U4.11 (SCK)
SCL: J2.3, J3.3, U1.4 (SCL), U2.4 (SCK), U3.27 (SCL), U4.27 (SCL)
SDA: J2.2, J3.2, U1.5 (SDA), U2.6 (SDI), U3.28 (SDA), U4.28 (SDA)
TX1: U3.15 (TX1), U4.15 (TX1)
USB: U3.19 (USB), U4.19 (USB)

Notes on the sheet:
Screw Terminals
Iridium
Power
Voltage Divider
IMU
Microcontroller
Adafruit Ultimate GPS
3V3
Adafruit M0 Proto
Battery
Sensor
GPS
12V
Mounting Holes

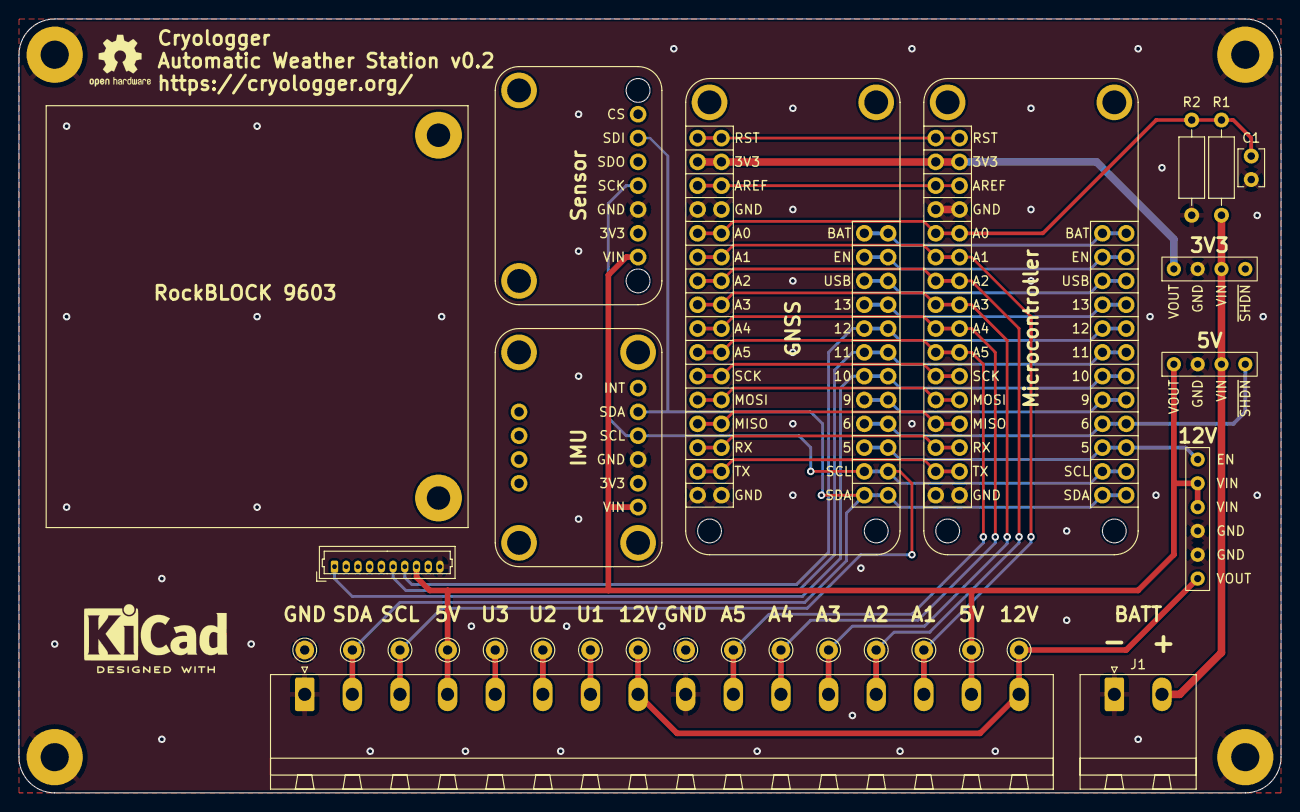
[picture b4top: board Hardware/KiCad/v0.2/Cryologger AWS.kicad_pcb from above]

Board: 2 copper layers, 134.6 x 82.5 mm, 19 parts (0 on the bottom side), 33 nets.
